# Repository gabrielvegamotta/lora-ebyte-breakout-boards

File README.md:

# eByte LoRa Breakout Boards
Breakout boards for LoRa modules from eByte.

This project came to be when I was trying/experimenting with LoRa for the first time. But the problem was the pin/pads of the module doesn't have the standart 2.54mm pin spacing for mounting on a breadboard/prefboard. So I created this breakout board to ease the use of this kind of module.

### Versions

 - [E22 Series](https://github.com/gabrielvegamotta/lora-ebyte-breakout-boards/tree/main/E22)

### References

 - [Sparkfun LoRa 1W Breakout](https://www.sparkfun.com/products/22792)
 - [EBYTE E28-2G4M27S 2.4GHz LoRa Breakout Board](https://www.openhardware.io/view/8304/E28-2G4M27S-24GHz-LoRa-Breakout-Board)
 - [EByte LoRa E22 E32 SMD adapter](https://www.pcbway.com/project/shareproject/EByte_LoRa_E22_E32_SMD_adapter.html?from=mischianti05)

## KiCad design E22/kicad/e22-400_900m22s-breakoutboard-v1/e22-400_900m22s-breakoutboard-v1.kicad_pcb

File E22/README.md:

# E22 Series

Breakout boards for the eByte LoRa modules, E22 series.

This breakout board can be use for the E22-400M22S and E22-900M22S. It uses 2.54mm pin headers so you can mount in a breadboard or perfboard. It has a mounting hole for coil/spring antennas.

There are two version: the complete breakout board and one with just the headers.

 - The complete version has an dedicated 3V3 LDO to power the module. Manual reset button, and some indicating LED.
 - The version with just the headers is really just the pins of the module conected directly to the headers.

### Documentation

Completed Version:

- [Schematic](https://github.com/gabrielvegamotta/lora-ebyte-breakout-boards/blob/main/E22/pdfs/SCH-e22-400_900m22s-breakoutboard-v1.pdf)
- [Layout](https://github.com/gabrielvegamotta/lora-ebyte-breakout-boards/blob/main/E22/pdfs/PCB-e22-400_900m22s-breakoutboard-v1.pdf)
- [BOM](https://github.com/gabrielvegamotta/lora-ebyte-breakout-boards/blob/main/E22/bom/ibom-e22-400_900m22s-breakoutboard-v1.html)

Just the Headers Version:

- [Schematic](https://github.com/gabrielvegamotta/lora-ebyte-breakout-boards/blob/main/E22/pdfs/SCH-e22-400_900m22s-breakoutboard-v1.pdf)
- [Layout](https://github.com/gabrielvegamotta/lora-ebyte-breakout-boards/blob/main/E22/pdfs/PCB-e22-400_900m22s-breakout-justheaders.pdf)

### PCB Assembled

More info soon.

### Performance & Results

More info soon.

### Final Thoughts

More info soon.

### References

 - [E22-400M22S Product Specifications](https://www.cdebyte.com/products/E22-400M22S)
 - [E22-900M22S Product Specifications](https://www.cdebyte.com/products/E22-900M22S)
 - [SX1262 Product Specifications](https://www.semtech.com/products/wireless-rf/lora-connect/sx1262)
 - [SX1268 Product Specifications](https://www.semtech.com/products/wireless-rf/lora-connect/sx1268)

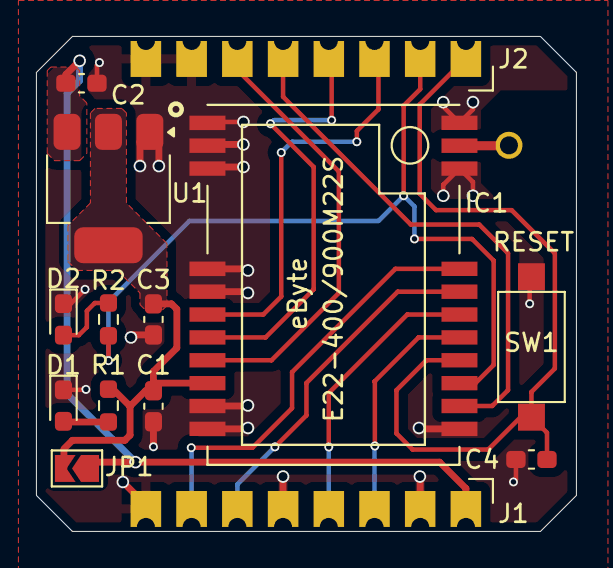
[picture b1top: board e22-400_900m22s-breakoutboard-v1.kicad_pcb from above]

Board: 2 copper layers, 30.0 x 27.5 mm, 15 parts (0 on the bottom side), 16 nets.

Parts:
C1, C2, C3, C4: 100nF; C_0603_1608Metric_Pad1.08x0.95mm_HandSolder
D1: LED_ON; LED_0603_1608Metric_Pad1.05x0.95mm_HandSolder
D2: LED_BUSY; LED_0603_1608Metric_Pad1.05x0.95mm_HandSolder
H1: COIL-ANTENA-MOUTING-HOLE; MountingHole_2.2mm_M2_DIN965_Pad
IC1: E22-900M22S
J1, J2: Conn_01x08_Pin; PinHeader_1x08_P2.54mm_Vertical
JP1: SolderJumper_2_Open; SolderJumper-2_P1.3mm_Open_TrianglePad1.0x1.5mm
R1, R2: 1K; R_0603_1608Metric_Pad0.98x0.95mm_HandSolder
SW1: LORA_RESET; SW_SPST_CK_RS282G05A3
U1: AMS1117-3.3; SOT-223-3_TabPin2

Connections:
+3V3: C1.1, C3.1, IC1.9 (VCC), JP1.2 (B), R1.1, U1.2 (VO)
/ANT: H1.1, IC1.21 (ANT)
/BUSY: IC1.14 (BUSY), J2.2, R2.1
/DIO1: IC1.13 (DIO1), J2.5
/DIO2: IC1.8 (DIO2), J2.6
/MISO: IC1.16 (MISO), J1.3
/MOSI: IC1.17 (MOSI), J1.4
/NRST: C4.2, IC1.15 (NRST), J2.1, SW1.1
/NSS: IC1.19 (NSS), J1.7
/RXEN: IC1.6 (RXEN), J2.3
/SCK: IC1.18 (SCK), J1.6
/TXEN: IC1.7 (TXEN), J2.4
GND: C1.2, C2.2, C3.2, C4.1, D1.1 (K), D2.1 (K), IC1.1 (GND), IC1.2 (GND), IC1.3 (GND), IC1.4 (GND), IC1.5 (GND), IC1.10 (GND), IC1.11 (GND), IC1.12 (GND), IC1.20 (GND), IC1.22 (GND), J1.2, J1.5, J1.8, J2.7, J2.8, SW1.2, U1.1 (GND)
unnamed: D1.2 (A), R1.2
unnamed: D2.2 (A), R2.2
VCC: C2.1, J1.1, JP1.1 (A), U1.3 (VI)

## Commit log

2024-04-07 Created project. Add sch sheet template
2024-04-07 Update sch add breakout pins, reset button
2024-04-07 Update sch, values of caps LDO. Add res and led for power on.
2024-04-07 Updated sch
2024-04-07 Initial layout of components. Initial pcb size and shape
2024-04-07 Changed breakout pin headers from 6 to 8 pins
2024-04-07 Layout and routing
2024-04-07 Add custom dru jlcpcb
2024-04-07 Add datasheets
2024-04-12 Add version just the headers
2024-04-12 Created pdf of layout
2024-04-12 Created gerber files
2024-04-12 Adjusted dimension description. Created new pdf
2024-04-12 Organized files on a different folder
2024-04-16 Add led for busy pin. Layout Adjusted
2024-04-16 Updated title block. Sch finished
2024-04-16 Updated title block. Pcb finished
2024-04-16 Created pdfs sch and pcb
2024-04-16 Created gerber files from gerber to order
2024-04-27 Created iBom breakoutboard v1
2024-04-27 Add readme for e22 series
2024-04-27 Created pdf sch
2024-04-27 Updated status in title block sch
